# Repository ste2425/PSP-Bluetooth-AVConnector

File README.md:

# PSP Bluetooth *AV Connector*

This forms part of my PSP Bluetooth project. Here you will find hardware files to build your own boards that can interface with the PSP 2000 and 3000 models AVPort.

There are also some sample boards i have designed for reference.

Check out the latest [Release](https://github.com/ste2425/AVBreakout/releases) for the libray files and sample files.

## Having boards made

Check out the guide [Here](./documentation/manufacturing.md) for information on how to have the samples made with PCBWay.

## The PSP Bluetooth Project

This is a part of the PSP Bluetooth project, to find information on the other components that make up this project please look here: https://github.com/psp-bluetooth

## Acknowledgements

The work ive done is just a thin layer ontop of work many other people have done, Iv'e also had lots of help from others.

* TokyoDrift - Originally created work that uses the SIO port to allow external controllers back around 2010. Since uploaded to Github
* OPDitto project - A project that uses the SIO port to allow for a real second analog stick. Its SIO implementation has been extremly helpful to me. Repo Here
* X41 - Shared with me an initial working SIO hello world app back when i could barely compile PSP code. This was invaluable in helping me get the hardware working right at the start of the project.
* PSP Homebrew Discord - Full of incredibly smart and helpful people too many to list individually. Without their help I'd never have managed to complete any of this.

---

* [Designing your own boards](#designing-your-own-boards) 
* [Samples](#samples)
  * [AV-Connector-Breakout](#av-connector-breakout)
  * [Dev-Board](#dev-board)
* [Damage to the PSP](#damage-to-the-psp)
* [Gotchas](#gotchas)
* [Connector pinout](#connector-pinout)

# Designing your own boards

If you wish to design your own boards to interface with the PSP AVConnector you can download the KiCad symbols and footprints to include in your project.

Download the latest release. Inside the `library` folder you will find a `psp.pretty` folder and a `psp.kicad_sym` file. These are the `footprints` and `symbols` respectively.

To install;

**Symbols**
* Open the Kicad project (not the schematic/pcb editor)
* Click `Preferences` -> `Manage Symbol Libraries`
* Choose if you want to install the library globally or project specific
* Click the `+` icon to add a new row.
* Give it the knickname `psp`
* Select the `psp.kicak_sym` file from wherever you saved it

**Footprints**
* Open the Kicad project (not the schematic/pcb editor)
* Click `Preferences` -> `Manage Footprint Libraries`
* Choose if you want to install the library globally or project specific
* Click the `+` icon to add a new row.
* Give it the knickname `psp`
* Select the `psp.pretty` folder from wherever you saved it

# Samples

There are a number of samples in the project. If you wish to load them in Kicad clone the repository and open the project.

If you just wish to have them produced, download the latest release and you will find them inside the `samples` folder. I have mine produced by `PCBWay` so my BOM files are built for them.

## AV-Connector-Breakout

This is a simple breakout of every pin in the AV port on the PSP. It has no other parts so will require no assembly. 

This is a small PCB intended for you to solder a cable to.

## Dev-Board

This is a all in one development board. It has the footprints to fit an ESP32 development module.

It also has the required logic level translators connected to pins <TODO ADD PINS>.

It has the TVOut connector footprint and all pins connected so you can use a original TVOut cable if you wish.

It is what i have been using to build my homebrew.

# Damage to the PSP

You should bevel, slightly curve, all the edges of the `TV out connector` that plugs into the PSP. So the edges are not all perfect 90deg angles. Otherwise it could damage the contacts. This will need to be manually done.

# Gotchas

* For the PSP to detect an AV cable connected it needs the heaphones cable connected. If your using the `Pass-Through` sample or degining your own PCB to use video output you will need to connect a headphones cable otherwise the PSP will not output video.
* Use of the serial port does *not* need a headphones cable connected unlike video output.
* The PSP's serial port does not operate at `5v` or `3.3v` like most MCU's you will try to interface with (Arduino, ESP32 etc). You will need to use a `Logic Level Converter`, some of the samples have one built in.
* The TV Connector would need to be manually soldered, they are difficult and require hot air. I source mine from `ZedLabz` https://www.zedlabz.com/products/headphone-socket-for-sony-psp-2000-3-5mm-jack-port-repair-part-internal-replacement-zedlabz

# Connector pinout

Openng a sample in Kicad and looking at either of the components will reveal the connector pinout. However you can reference https://www.psdevwiki.com/psp/Serial_Adapter also.

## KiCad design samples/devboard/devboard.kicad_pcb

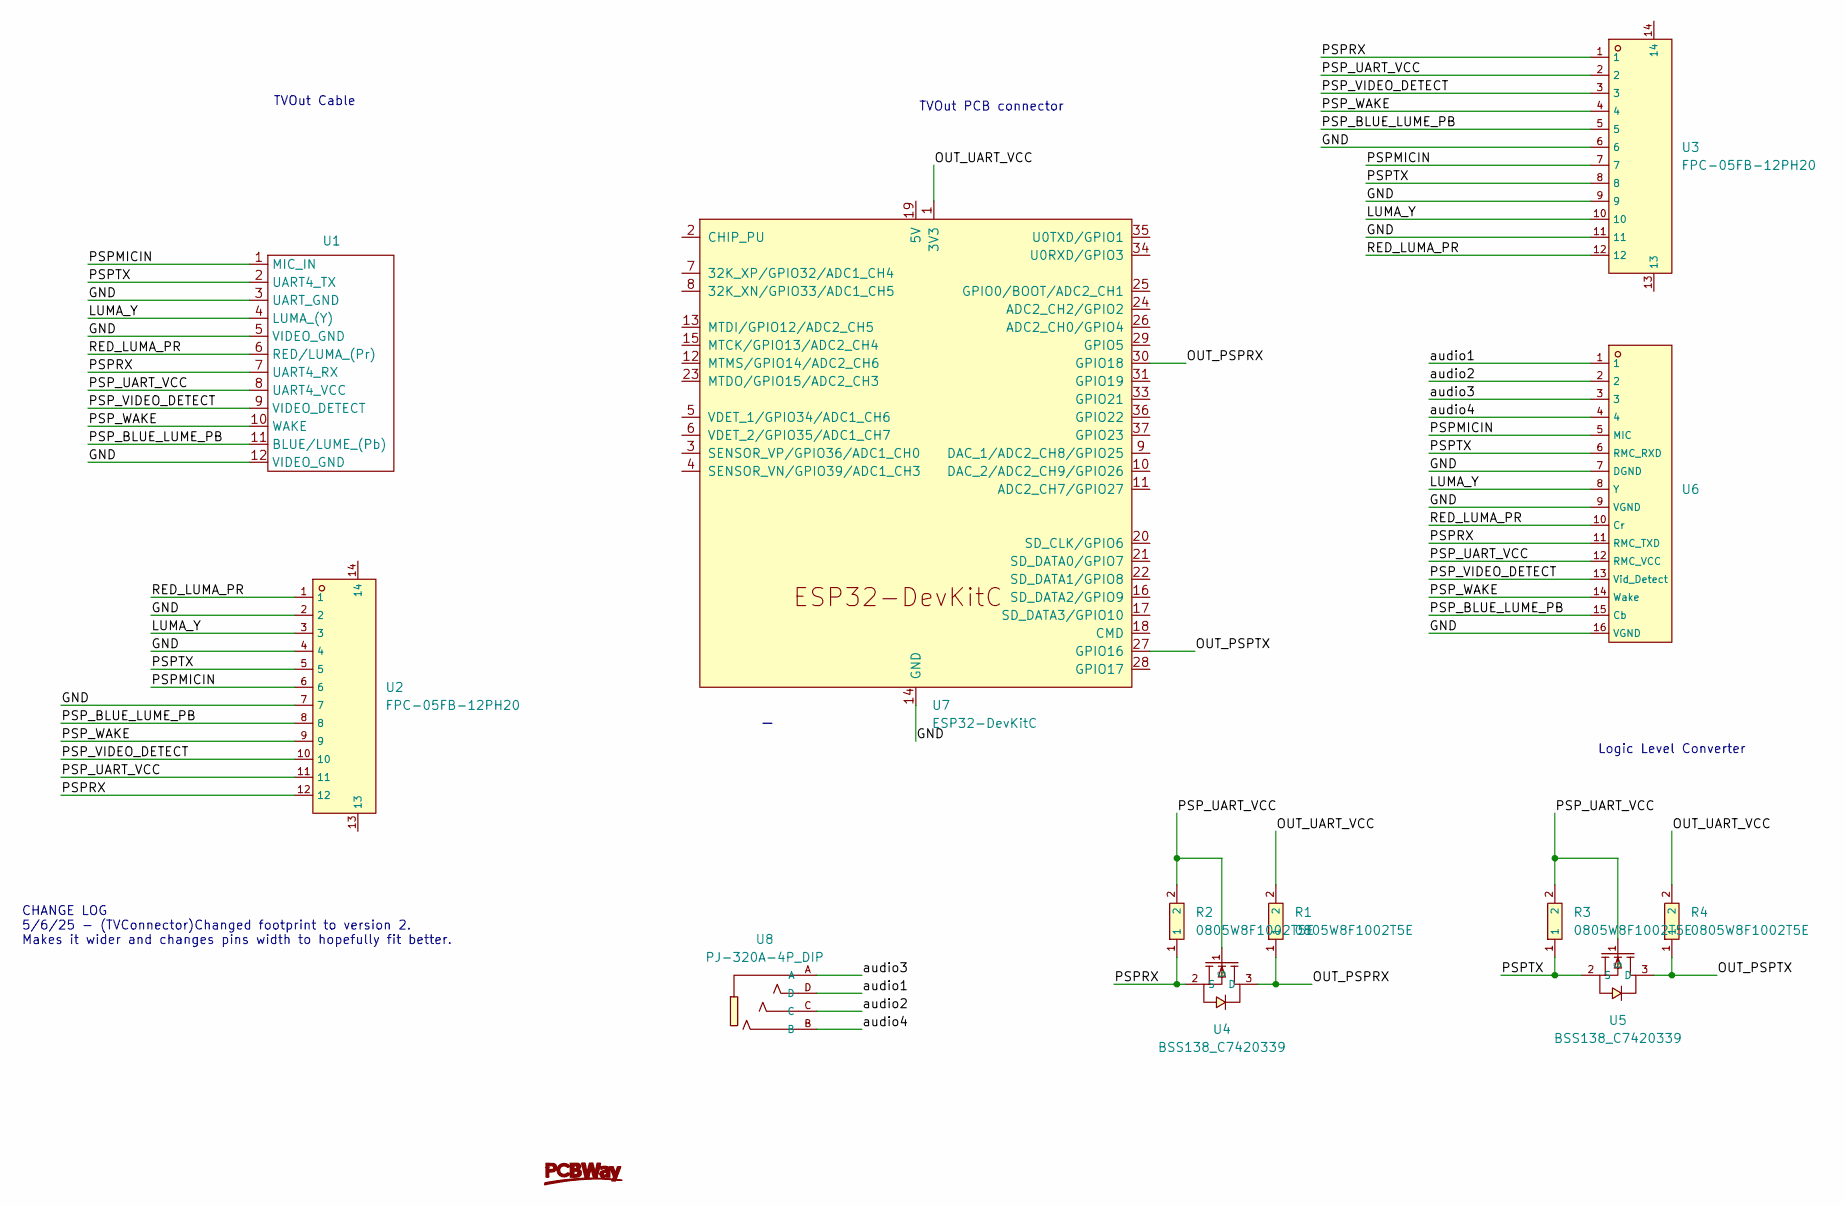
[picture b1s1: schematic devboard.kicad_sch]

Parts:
R1, R2, R3, R4: 0805W8F1002T5E; R0805; LCSC C17414
U1: TVOut Cable
U2, U3: FPC-05FB-12PH20; FPC-SMD_12P-P0.50_XUNPU_FPC-05FB-12PH20; LCSC C2856829
U4, U5: BSS138_C7420339; SOT-23-3_L2.9-W1.3-P1.90-LS2.4-BR; LCSC C7420339
U6: TVOut Connector
U7: ESP32-DevKitC
U8: PJ-320A-4P_DIP; AUDIO-TH_PJ-320A-4P-DIP; LCSC C18185602

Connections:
/GND: U1.3 (UART_GND), U1.5 (VIDEO_GND), U1.12 (VIDEO_GND), U2.2, U2.4, U2.7, U3.6, U3.9, U3.11, U6.7 (DGND), U6.9 (VGND), U6.16 (VGND), U7.14 (GND), U7.32 (GND), U7.38 (GND)
/LUMA_Y: U1.4 (LUMA_(Y)), U2.3, U3.10, U6.8 (Y)
/OUT_PSPRX: R1.1, U4.3 (D), U7.30 (GPIO18)
/OUT_PSPTX: R4.1, U5.3 (D), U7.27 (GPIO16)
/OUT_UART_VCC: R1.2, R4.2, U7.1 (3V3)
/PSPMICIN: U1.1 (MIC_IN), U2.6, U3.7, U6.5 (MIC)
/PSPRX: R2.1, U1.7 (UART4_RX), U2.12, U3.1, U4.2 (S), U6.11 (RMC_TXD)
/PSPTX: R3.1, U1.2 (UART4_TX), U2.5, U3.8, U5.2 (S), U6.6 (RMC_RXD)
/PSP_BLUE_LUME_PB: U1.11 (BLUE/LUME_(Pb)), U2.8, U3.5, U6.15 (Cb)
/PSP_UART_VCC: R2.2, R3.2, U1.8 (UART4_VCC), U2.11, U3.2, U4.1 (G), U5.1 (G), U6.12 (RMC_VCC)
/PSP_VIDEO_DETECT: U1.9 (VIDEO_DETECT), U2.10, U3.3, U6.13 (Vid_Detect)
/PSP_WAKE: U1.10 (WAKE), U2.9, U3.4, U6.14 (Wake)
/RED_LUMA_PR: U1.6 (RED/LUMA_(Pr)), U2.1, U3.12, U6.10 (Cr)
/audio1: U6.1, U8.D
/audio2: U6.2, U8.C
/audio3: U6.3, U8.A
/audio4: U6.4, U8.B

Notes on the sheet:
Logic Level Converter
TVOut PCB connector
TVOut Cable
CHANGE LOG 5/6/25 - (TVConnector)Changed footprint to version 2. Makes it wider and changes pins width to hopefully fit better.

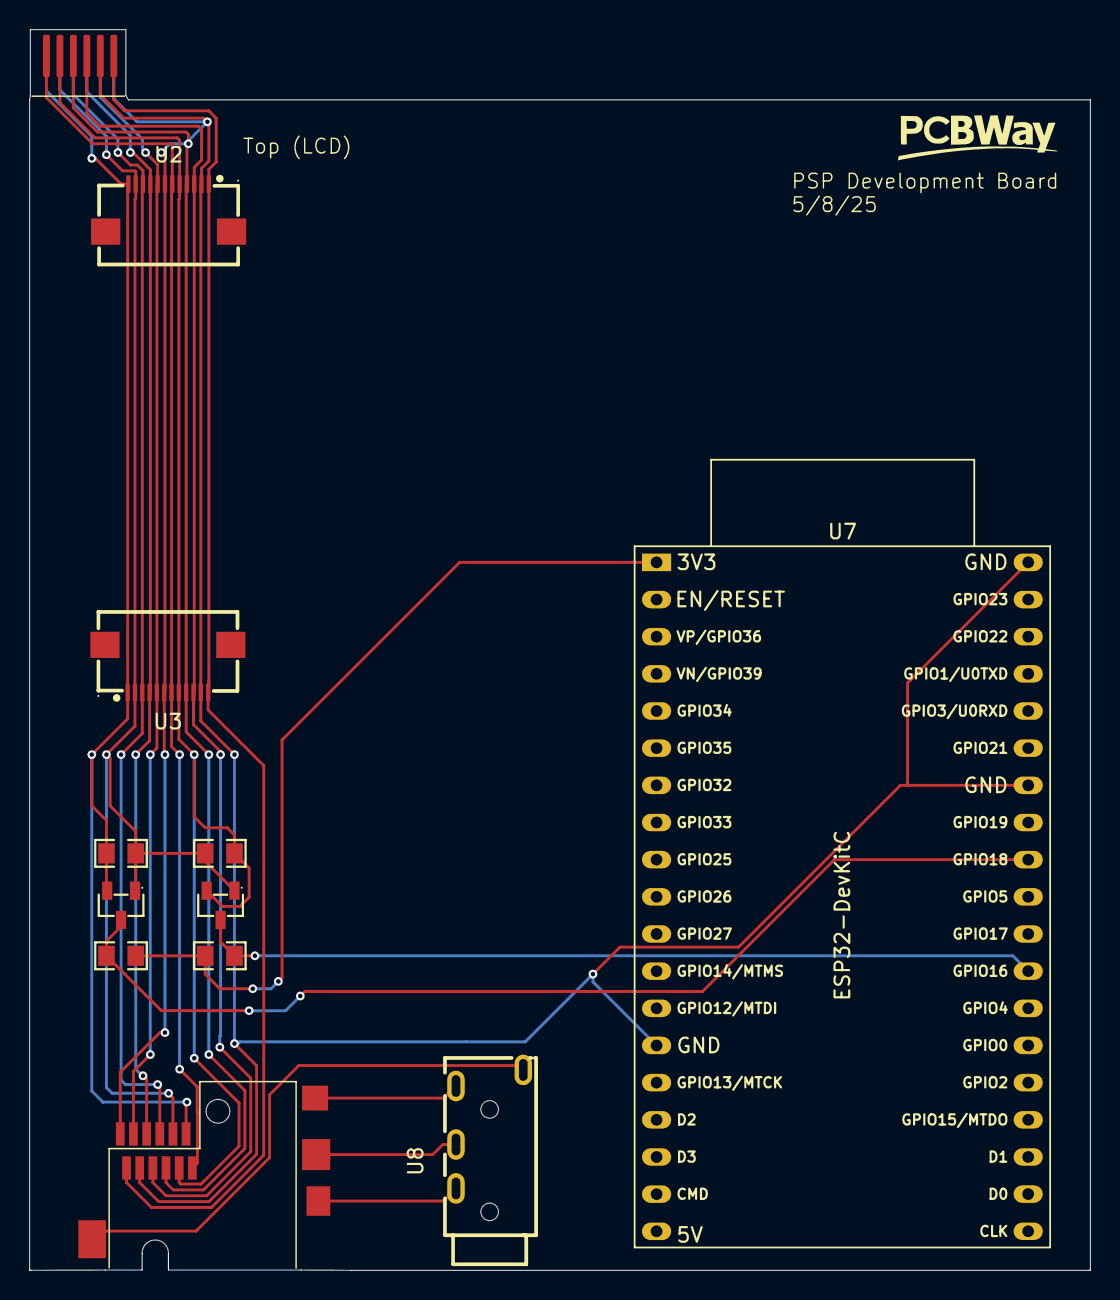
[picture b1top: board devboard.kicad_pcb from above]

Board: 2 copper layers, 72.5 x 84.8 mm, 12 parts (0 on the bottom side), 17 nets.

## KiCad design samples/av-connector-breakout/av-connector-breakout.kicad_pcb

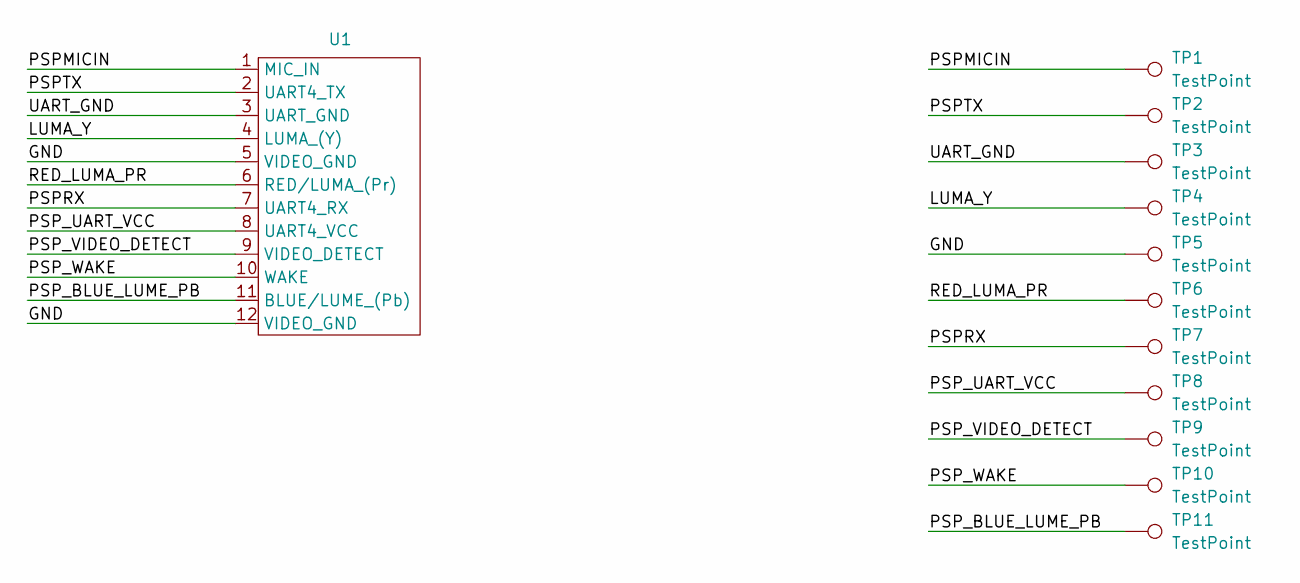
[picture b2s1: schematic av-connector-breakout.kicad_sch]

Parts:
TP1, TP2, TP3, TP4, TP5, TP6, TP7, TP8, TP9, TP10, TP11: TestPoint; TestPoint_Pad_1.0x1.0mm
U1: TVOut Cable

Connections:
/GND: TP5.1, U1.5 (VIDEO_GND), U1.12 (VIDEO_GND)
/LUMA_Y: TP4.1, U1.4 (LUMA_(Y))
/PSPMICIN: TP1.1, U1.1 (MIC_IN)
/PSPRX: TP7.1, U1.7 (UART4_RX)
/PSPTX: TP2.1, U1.2 (UART4_TX)
/PSP_BLUE_LUME_PB: TP11.1, U1.11 (BLUE/LUME_(Pb))
/PSP_UART_VCC: TP8.1, U1.8 (UART4_VCC)
/PSP_VIDEO_DETECT: TP9.1, U1.9 (VIDEO_DETECT)
/PSP_WAKE: TP10.1, U1.10 (WAKE)
/RED_LUMA_PR: TP6.1, U1.6 (RED/LUMA_(Pr))
/UART_GND: TP3.1, U1.3 (UART_GND)

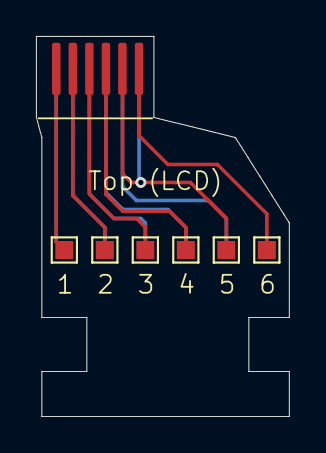
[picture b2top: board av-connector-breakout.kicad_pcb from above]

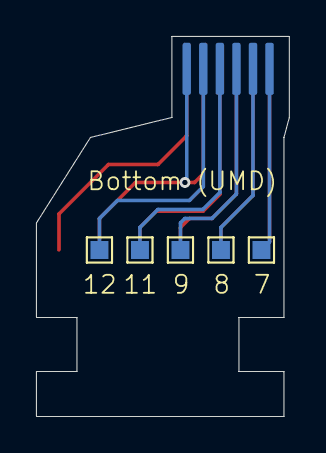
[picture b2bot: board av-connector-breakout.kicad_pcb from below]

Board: 2 copper layers, 14.0 x 21.1 mm, 12 parts (5 on the bottom side), 11 nets.

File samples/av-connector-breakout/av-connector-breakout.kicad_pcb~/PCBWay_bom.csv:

Designator,Quantity,Value,Footprint,Package,MPN,DNP,Mount_Type,Description
"TP1, TP10, TP11, TP2, TP3, TP4, TP5, TP6, TP7, TP8, TP9",11,TestPoint,TestPoint_Pad_1.0x1.0mm,,,,tht,test point
U1,1,~,TVOut Cable,,,,smt,

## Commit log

2025-05-14 initial
2025-06-08 Added logo
2025-07-07 restructure and widen tvout connector
2025-07-09 clean up repo. Pretty much done i think
2025-07-09 restore logo
2025-07-09 clean up readme
2025-09-19 clean up repo
2025-10-06 Added docs
